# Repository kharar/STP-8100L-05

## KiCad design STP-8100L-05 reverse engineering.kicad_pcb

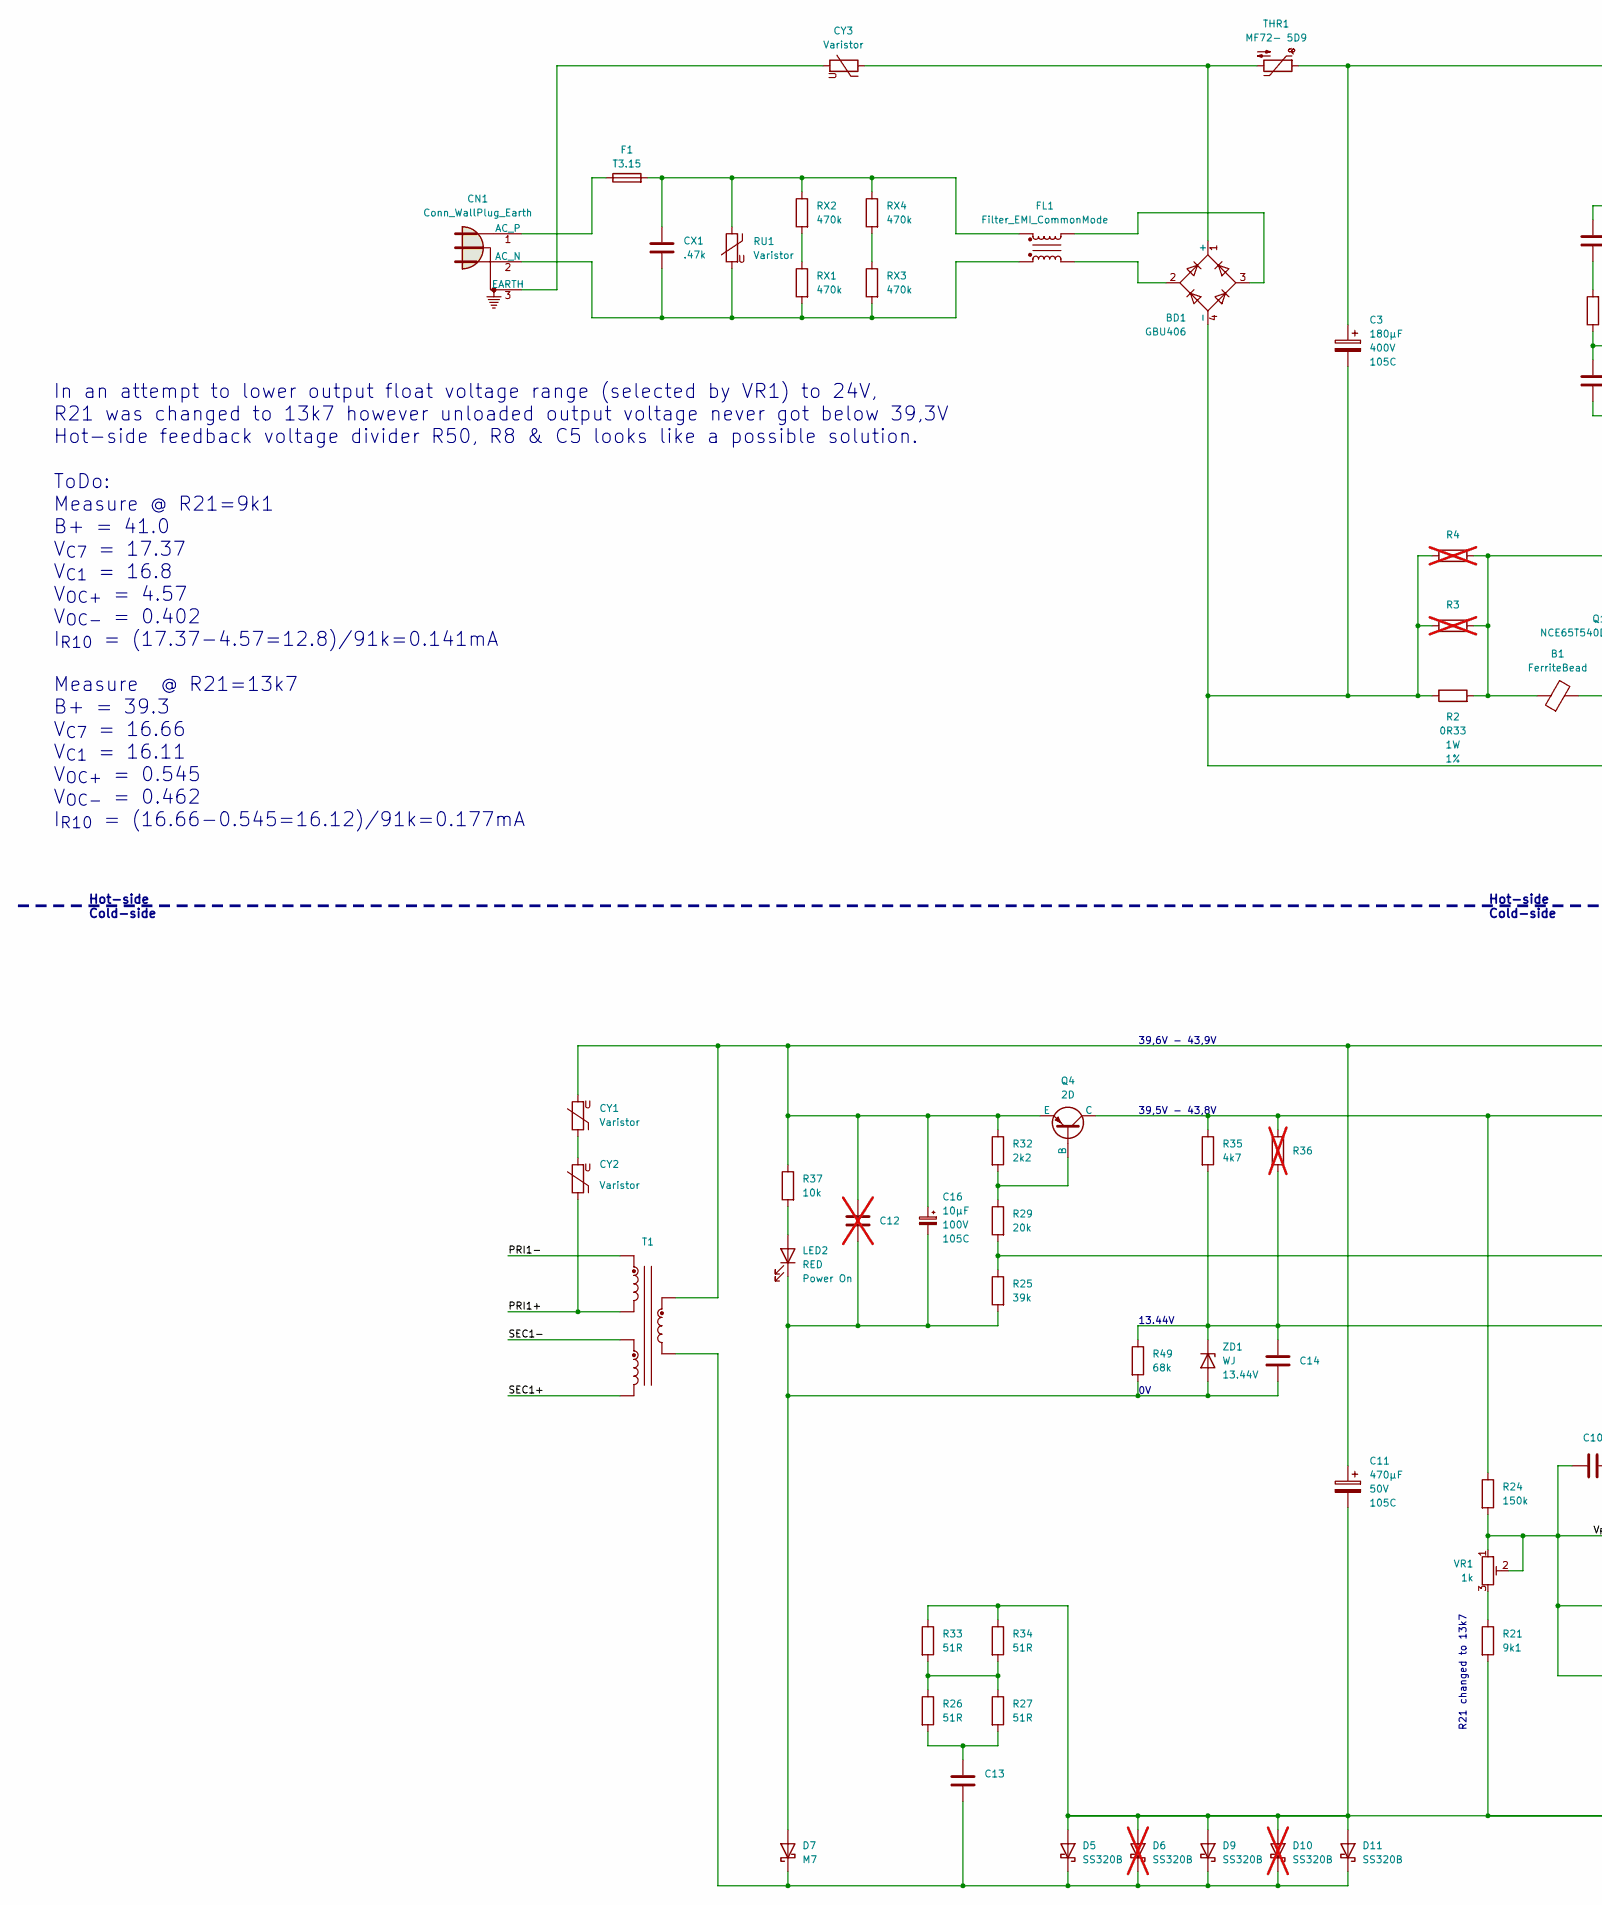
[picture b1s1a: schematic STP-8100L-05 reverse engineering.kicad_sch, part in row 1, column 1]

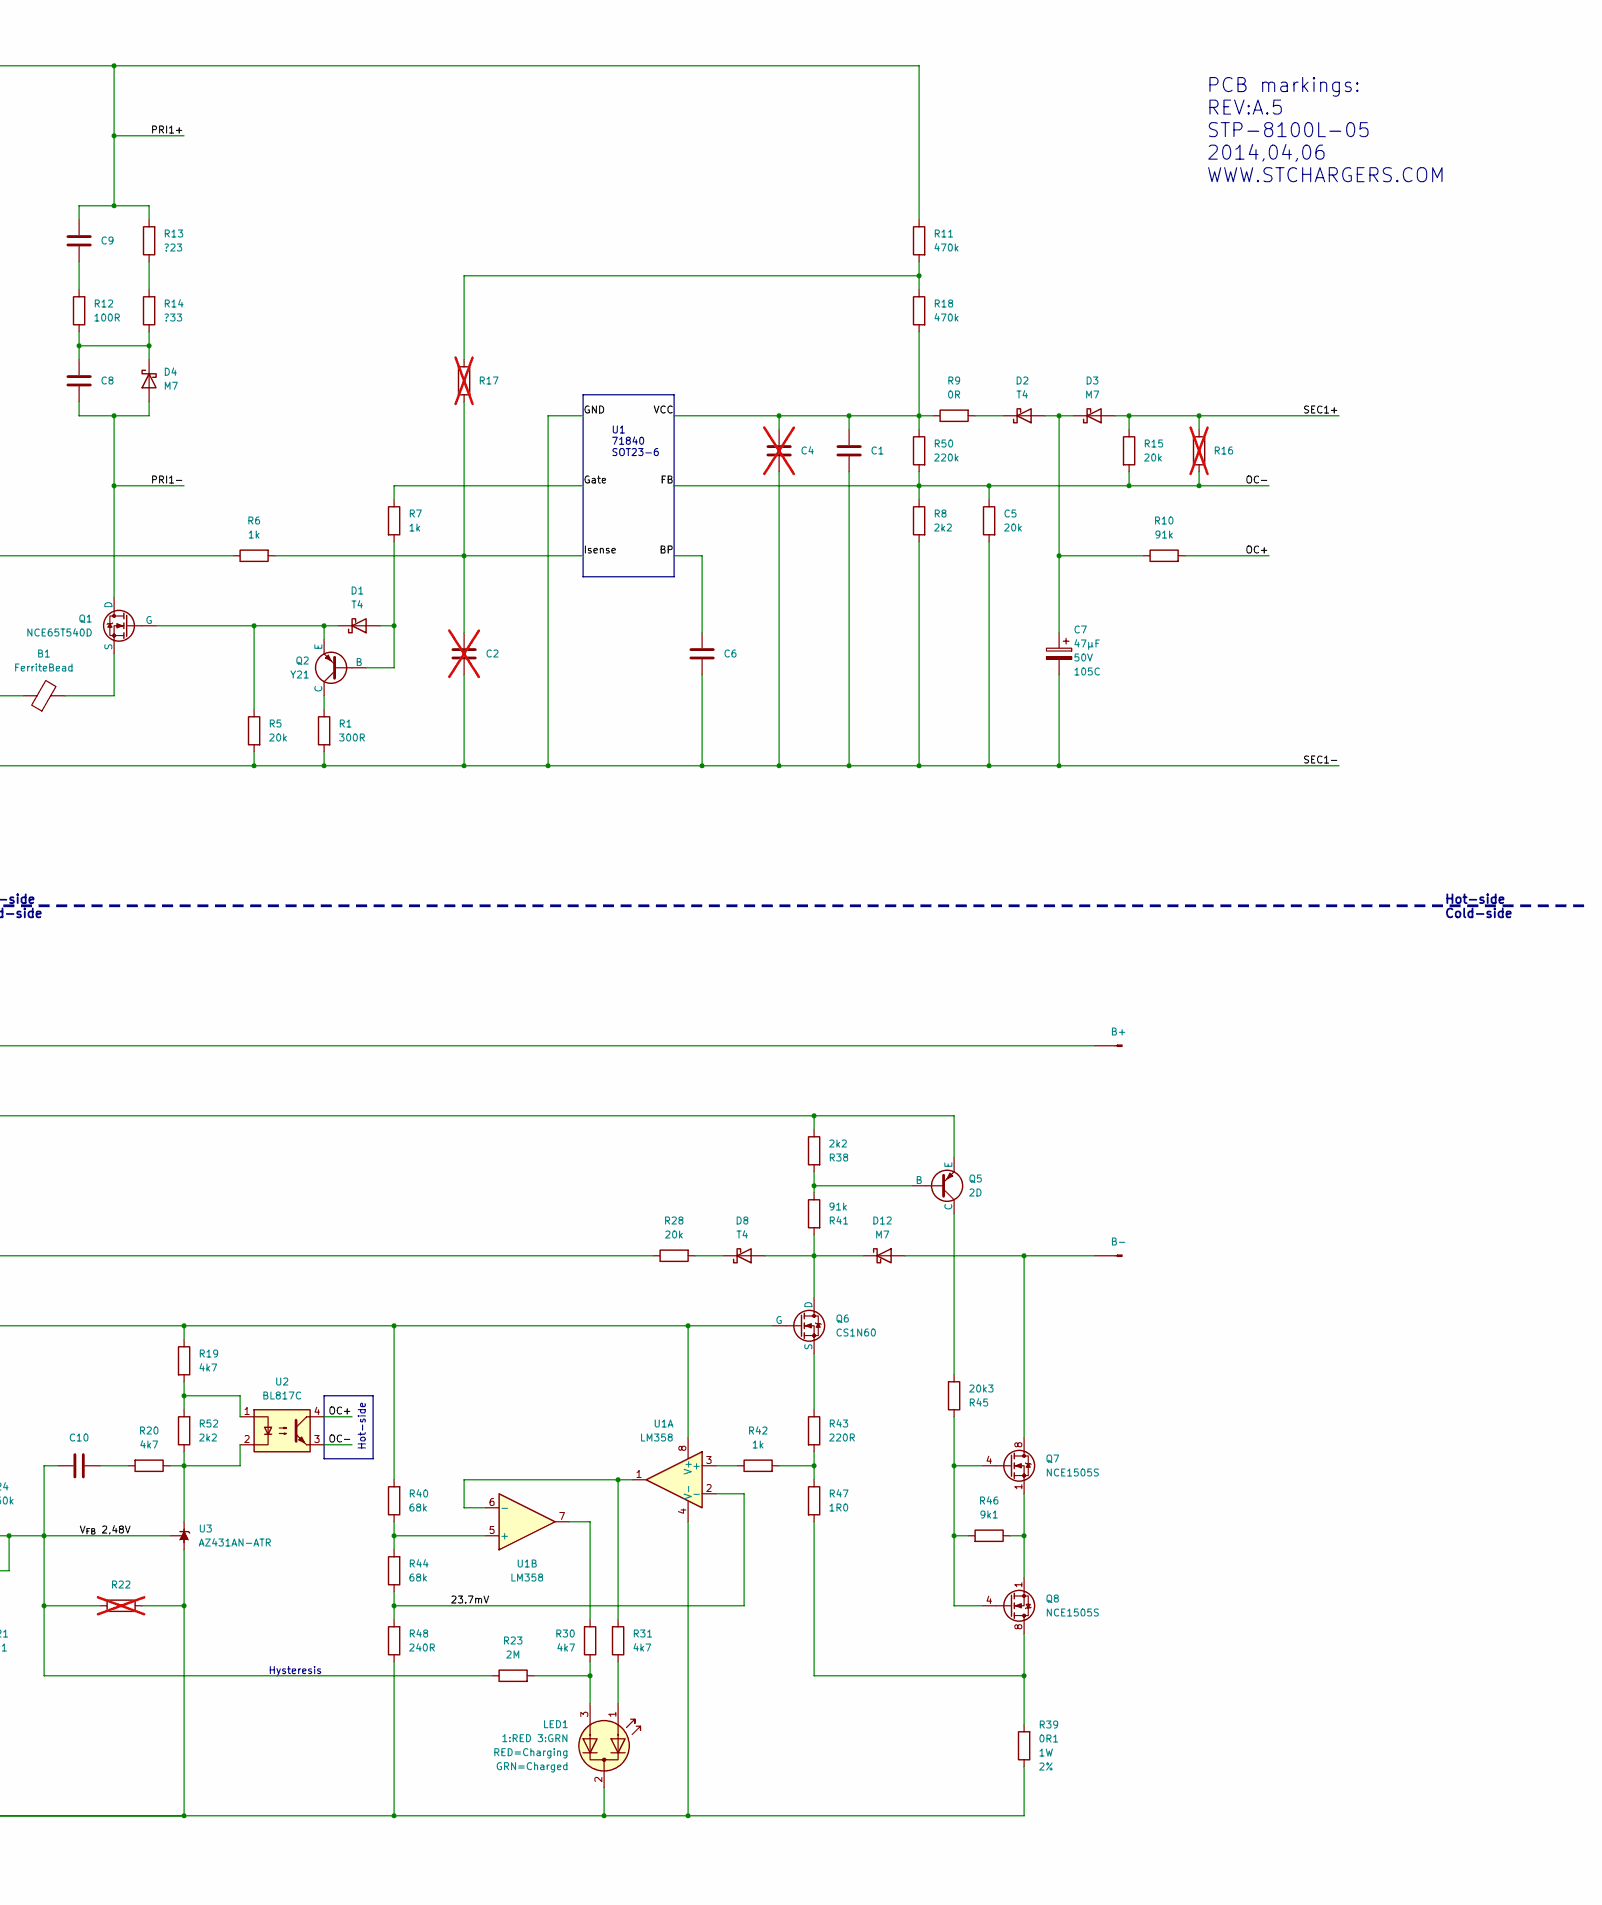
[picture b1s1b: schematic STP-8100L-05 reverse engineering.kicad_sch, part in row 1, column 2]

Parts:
B1: FerriteBead; L_1206_3216Metric
BD1: GBU406; Diode_Bridge_Vishay_GBU
C1, C6, C8, C9, C13: C_1206_3216Metric
C2, C4, C12: C_0805_2012Metric; not fitted
C3: 180µF; CP_Radial_D25.0mm_P10.00mm_SnapIn; Voltage 400V
C5: 20k; R_0805_2012Metric
C7: 47µF; CP_Radial_D6.3mm_P2.50mm; Voltage 50V
C10, C14: C_0805_2012Metric
C11: 470µF; CP_Radial_D12.5mm_P5.00mm; Voltage 50V
C16: 10µF; CP_Radial_D5.0mm_P2.50mm; Voltage 100V
CN1: Conn_WallPlug_Earth
CX1: .47k
CY1, CY2, CY3: Varistor; RV_Disc_D7mm_W3.5mm_P5mm
D1, D2, D8: ?; D_SOD-123
D3, D4, D7, D12: M7; D_SMA
D5, D9, D11: SS320B; D_SMA
D6, D10: SS320B; D_SMA; not fitted
F1: T3.15
FL1: Filter_EMI_CommonMode
J1: B-; TestPoint_THTPad_D4.0mm_Drill2.0mm
J2: B+; TestPoint_THTPad_D4.0mm_Drill2.0mm
LED1: 1:RED 3:GRN; LED_D5.0mm-3
LED2: RED; LED_D5.0mm_Clear
Q1: NCE65T540D; TO-263-3_TabPin2
Q2: Y21; SOT-23
Q4, Q5: 2D; SOT-23
Q6: CS1N60; TO-252-2
Q7, Q8: NCE1505S; SOIC-8_3.9x4.9mm_P1.27mm
R1: 300R; R_1206_3216Metric
R2: 0R33; R_Axial_DIN0516_L15.5mm_D5.0mm_P5.08mm_Vertical; Tolerance 1%
R3, R4, R17: R_1206_3216Metric; not fitted
R5: 20k; R_1206_3216Metric
R6, R42: 1k; R_0805_2012Metric
R7: 1k; R_1206_3216Metric
R8, R32, R38, R52: 2k2; R_0805_2012Metric
R9: 0R; R_1206_3216Metric
R10, R41: 91k; R_0805_2012Metric
R11, R18: 470k; R_1206_3216Metric
R12: 100R; R_1206_3216Metric
R13: ?23; R_1206_3216Metric
R14: ?33; R_1206_3216Metric
R15, R28, R29: 20k; R_0805_2012Metric
R16, R22, R36: R_0805_2012Metric; not fitted
R19, R20, R30, R31, R35: 4k7; R_0805_2012Metric
R21, R46: 9k1; R_0805_2012Metric
R23: 2M; R_0805_2012Metric
R24: 150k; R_0805_2012Metric
R25: 39k; R_0805_2012Metric
R26, R27, R33, R34: 51R; R_0805_2012Metric
R37: 10k; R_0805_2012Metric
R39: 0R1; R_Axial_DIN0516_L15.5mm_D5.0mm_P5.08mm_Vertical; Tolerance 2%
R40, R44, R49: 68k; R_0805_2012Metric
R43: 220R; R_2010_5025Metric
R45: 20k3; R_0805_2012Metric
R47: 1R0; R_0805_2012Metric
R48: 240R; R_0805_2012Metric
R50: 220k; R_0805_2012Metric
RU1: Varistor; RV_Disc_D7mm_W3.5mm_P5mm
RX1, RX2, RX3, RX4: 470k; R_1206_3216Metric
T1: (no value)
THR1: MF72- 5D9
U1: LM358; SO-8_3.9x4.9mm_P1.27mm
U2: BL817C; DIP-4_W7.62mm
U3: AZ431AN-ATR; SOT-23
VR1: 1k; Potentiometer_Bourns_3214J_Horizontal
ZD1: WJ; D_SOD-123; Voltage 13.44V

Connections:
/23.7mV: R44.1, R48.2, U1.2 (-)
/BP: C6.1
/FB: C5.1, R8.1, R15.2, R16.2, R50.2, U2.3
/GND: BD1.4 (-), C1.2, C2.2, C3.2, C4.2, C5.2, C6.2, C7.2, R1.2, R2.1, R3.1, R4.1, R5.2, R8.2, T1.4
/Gate: R7.1
/Isense: C2.1, R6.2, R17.2
/OC+: R10.2, U2.4
/PRI1+: C3.1, C9.1, CY2.1, R11.1, R13.2, T1.6, THR1.1
/PRI1-: C8.2, D4.2 (A), Q1.1 (D), T1.3
/SEC1+: D3.2 (A), R15.1, R16.1, T1.5
/VCC: C1.1, C4.1, R9.1, R18.2, R50.1
/V_{FB} 2,48V: C10.2, R22.1, R23.1, R24.2, U3.2 (REF), VR1.1, VR1.2
unnamed: B1.1, R2.2, R3.2, R4.2, R6.1
unnamed: BD1.1 (+), CY3.1, THR1.2
unnamed: BD1.2, FL1.4
unnamed: BD1.3, FL1.2
unnamed: C9.2, R12.2
unnamed: C10.1, R20.2
unnamed: C13.1, R26.2, R27.2
unnamed: CN1.2 (AC_N), CX1.2, FL1.3, RU1.2, RX1.2, RX3.2
unnamed: CN1.3 (EARTH), CY3.2
unnamed: CN1.1 (AC_P), F1.1
unnamed: CX1.1, F1.2, FL1.1, RU1.1, RX2.1, RX4.1
unnamed: CY1.1, CY2.2
unnamed: D1.2 (A), Q2.2 (B), R7.2
unnamed: D1.1 (K), Q1.2 (G), Q2.3 (E), R5.1
unnamed: C7.1, D2.2 (A), D3.1 (K), R10.1
unnamed: D2.1 (K), R9.2
unnamed: C8.1, D4.1 (K), R12.1, R14.1
unnamed: C12.1, C14.1, C16.2, D7.2 (A), LED2.1 (K), R25.2, R49.2, ZD1.2 (A)
unnamed: D8.1 (K), R28.2
unnamed: C11.2, D5.2 (A), D6.2 (A), D9.2 (A), D10.2 (A), D11.2 (A), LED1.2 (K), R21.2, R22.2, R33.1, R34.1, R39.1, R48.1, U1.4 (V-), U3.3 (A)
unnamed: C13.2, D5.1 (K), D6.1 (K), D7.1 (K), D9.1 (K), D10.1 (K), D11.1 (K), T1.8
unnamed: D12.2 (A), J1.1, Q7.5 (D), Q7.6 (D), Q7.7 (D), Q7.8 (D)
unnamed: D8.2 (A), D12.1 (K), Q6.1 (D), R41.2
unnamed: C11.1, C12.2, C16.1, CY1.2, J2.1, Q4.3 (E), R32.1, R37.1, T1.1
unnamed: LED1.1 (A1), R31.1
unnamed: LED1.3 (A2), R23.2, R30.1
unnamed: LED2.2 (A), R37.2
unnamed: B1.2, Q1.3 (S)
unnamed: Q2.1 (C), R1.1
unnamed: Q4.2 (B), R29.1, R32.2
unnamed: Q4.1 (C), Q5.3 (E), R24.1, R35.1, R36.1, R38.1
unnamed: Q5.2 (B), R38.2, R41.1
unnamed: Q5.1 (C), R45.2
unnamed: C14.2, Q6.2 (G), R19.1, R35.2, R36.2, R40.2, R49.1, U1.8 (V+), ZD1.1 (K)
unnamed: Q6.3 (S), R43.1
unnamed: Q7.4 (G), Q8.4 (G), R45.1, R46.2
unnamed: Q7.1 (S), Q7.2 (S), Q7.3 (S), Q8.1 (S), Q8.2 (S), Q8.3 (S), R46.1
unnamed: Q8.5 (D), Q8.6 (D), Q8.7 (D), Q8.8 (D), R39.2, R47.2
unnamed: R11.2, R17.1, R18.1
unnamed: R13.1, R14.2
unnamed: R19.2, R52.2, U2.1
unnamed: R21.1, VR1.3
unnamed: R25.1, R28.1, R29.2
unnamed: R26.1, R27.1, R33.2, R34.2
unnamed: R30.2, U1.7
unnamed: R42.2, R43.2, R47.1
unnamed: RX1.1, RX2.2
unnamed: RX3.1, RX4.2
unnamed: R42.1, U1.3 (+)
unnamed: R40.1, R44.2, U1.5 (+)
unnamed: R31.2, U1.1, U1.6 (-)
unnamed: R20.1, R52.1, U2.2, U3.1 (K)

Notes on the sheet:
R21 changed to 13k7
13.44V
Hysteresis
Hot-side Cold-side
Hot-side
39,5V - 43,8V
In an attempt to lower output float voltage range (selected by VR1) to 24V, R21 was changed to 13k7 however unloaded output voltage never got below 39,3V Hot-side feedback voltage divider R50, R8 & C5 looks like a possible solution. ToDo: Measure @ R21=9k1 B+ = 41.0 V_{C7} = 17.37 V_{C1} = 16.8 V_{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
U1 71840 SOT23-6
PCB markings: REV:A.5 STP-8100L-05 2014,04,06 WWW.STCHARGERS.COM
39,6V - 43,9V

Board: 2 copper layers, 104 parts (0 on the bottom side), 58 nets, no tracks yet.

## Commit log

2023-08-07 Add hot-side to schematics
2023-08-08 Rearrange and add measurements
2023-09-18 Last commit
